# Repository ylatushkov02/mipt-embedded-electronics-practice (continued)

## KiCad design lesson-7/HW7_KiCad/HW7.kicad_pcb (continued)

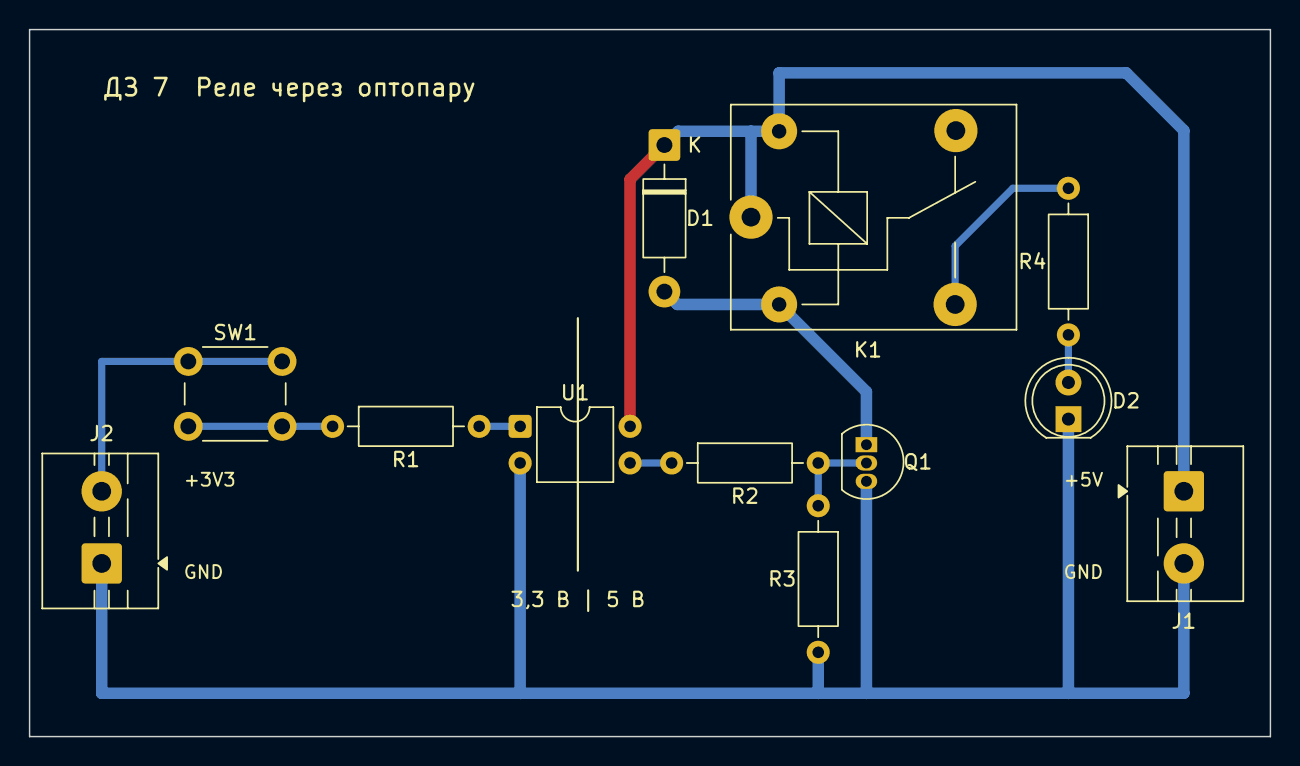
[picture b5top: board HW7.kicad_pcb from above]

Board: 2 copper layers, 86.0 x 49.0 mm, 12 parts (0 on the bottom side), 10 nets.

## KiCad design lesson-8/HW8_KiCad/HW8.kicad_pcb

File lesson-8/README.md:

# ДЗ № 8. Два канала управления реле, питание 12 В через LM317

## Задание
Плата управляет двумя независимыми нагрузками через реле 5 В:
- **Входные сигналы:** 3,3…5 В, ток не более 1…2 мА. Подаются на клеммник `IN1 | GND | IN2`.
- **Питание:** на плату приходит 12 В, напряжение 5 В для реле получается на стабилизаторе LM317T.
- **Выходы:** контакты NC, NO, COM каждого реле выведены на винтовые клеммники.
- **Индикация:** светодиод показывает, что реле включено.
- **Сборка:** монтажная плата, пайка.

## Схема
- **Питание:** U1 LM317T с делителем R1 330 Ом и R2 1 кОм даёт 5,1 В. C1 (0,1 мкФ) и C2 (10 мкФ) — фильтрующие конденсаторы. Жёлтый светодиод D5 с R10 1 кОм показывает, что +5 В есть.
- **Тестовые кнопки:** SW1 и SW2 подают +5 В на IN1 и IN2, чтобы проверить плату без микроконтроллера. Входной ток при нажатии — 1,95 мА. Пока подключён микроконтроллер, кнопки не нажимать.
- **Каналы.** В каждом канале стоит ключ на транзисторе BC547B:
  - сигнал со входа идёт через R3/R6 (2,2 кОм) на базу;
  - R4/R7 (10 кОм) держат транзистор закрытым, если вход ни к чему не подключён;
  - транзистор включает обмотку реле K1/K2 (T73-5VDC) и параллельно ей светодиод D2/D4 с резистором R5/R8 (330 Ом);
  - D1/D3 (1N4007) гасят выброс напряжения на обмотке при выключении.
- **Клеммники:** J1 — вход 12 В, J2 — `IN1 | GND | IN2`, J3/J4 — контакты `NC | NO | COM` реле 1 и 2.

## Расчёт
| Величина | Расчёт | Значение |
|---|---|---|
| Выход LM317 | 1,25 · (1 + 1000/330) + 50 мкА · 1 кОм | **5,09 В** |
| Ток делителя R1 | 1,25 / 330 | 3,8 мА ≥ 3,5 мА (минимальная нагрузка LM317) |
| Ток обмотки (худший случай, 55 Ом) | 5,09 / 55 | 93 мА < 100 мА (максимум BC547) |
| R5, R8 | (5,09 − 2,0 − 0,2) / 10 мА | 289 Ом → **330 Ом** |
| R3, R6 (вход ≤ 2 мА) | (5 − 0,8) / 2 мА | 2,1 кОм → **2,2 кОм** |
| Входной ток | при 5 В / при 3,3 В | 1,9 мА / 1,14 мА |
| Ток базы при 3,3 В | 1,14 − 0,08 (уходит через R4) | 1,06 мА > 93 / 100 = 0,93 мА, транзистор полностью открыт |
| Нагрузка 5 В (оба реле) | 2 · (93 + 8,8) + 3,8 | ≈ 208 мА |
| D5, R10 (индикатор +5 В) | (5,09 − 2,0) / 1 кОм | 3,1 мА; заодно нагружает LM317 до 6,9 мА в покое |
| Мощность LM317 | (12 − 5,09) · 0,208 | ≈ 1,4 Вт, нужен небольшой радиатор |

## Результат
Плата спаяна на монтажной плате 7 × 9 см и работает:
- **Питание:** при подаче 12 В горит жёлтый D5, стабилизатор выдаёт +5 В.
- **Входы:** сигнал 3,3 В подаётся с лабораторного блока питания через кнопки на макетке. Блок показывает ток около 0 А: он меньше 2 мА, поэтому на дисплее не виден.
- **Реле:** кнопка 1 включает реле K1 (щелчок, горит зелёный D2), кнопка 2 включает K2 (щелчок, горит красный D4).
- **Исправление при наладке:** в первой версии рисунка пайки транзисторы BC547 были развёрнуты неправильно (коллектор и эмиттер перепутаны), и реле не включались. Транзисторы развёрнуты плоской стороной вниз, после этого схема заработала.

## Файлы
| Файл | Что это |
|---|---|
| `HW8_KiCad/HW8.kicad_sch` | Принципиальная схема с расчётом, рамка ГОСТ |
| `HW8_KiCad/HW8.kicad_pcb` | Двусторонняя плата 116 × 78,5 мм: дорожки на двух слоях, переходные отверстия, размеры на User.Drawings, пояснения на User.Comments |
| `Схема_ДЗ8_предпросмотр.pdf` | Предпросмотр схемы |
| `Плата_ДЗ8_трассировка_предпросмотр.pdf` | Трассировка и сборочный чертёж |
| `Макетка_два_реле_LM317.png` | Сборка на макетной плате: питание 12 В от лабораторного БП, LM317, два канала реле |
| `Проверка_кнопками_схема_подключения.png` | Дополнительная проверка от 3,3 В: внешние кнопки на макетке подключаются к J2 |
| `Монтажная_плата_схема_пайки.png` | Пайка на монтажной плате 34 × 22 отверстия: вид сверху и вид снизу |
| `Монтажная_плата_итог_внешние_кнопки.png` | Итоговая раскладка пайки собранного варианта |
| `Фото_плата_сверху.png`, `Фото_плата_снизу.png`, `Фото_проверка_3.3В.png` | Фото собранной платы и стенда проверки |
| `Видео_работа_платы.mov` | Видео: кнопки включают реле 1 и 2 |

## Проверка работоспособности
1. Перед подачей питания прозвонить +12V–GND и +5V–GND: короткого замыкания быть не должно.
2. Подать 12 В на J1: загорается жёлтый D5. Мультиметром на C2 должно быть около 5,1 В.
3. Нажать SW1: K1 щёлкает, горит зелёный D2. Отпустить — реле отпускает.
4. Нажать SW2: K2 щёлкает, горит красный D4. Нажать обе — работают оба канала.
5. По желанию подключить нагрузку к COM–NO клеммника J3: она включается кнопкой SW1.
6. Проверка от 3,3 В (как от микроконтроллера) — по схеме `Проверка_кнопками_схема_подключения.png`: внешние кнопки на макетке подключаются к клеммнику J2.

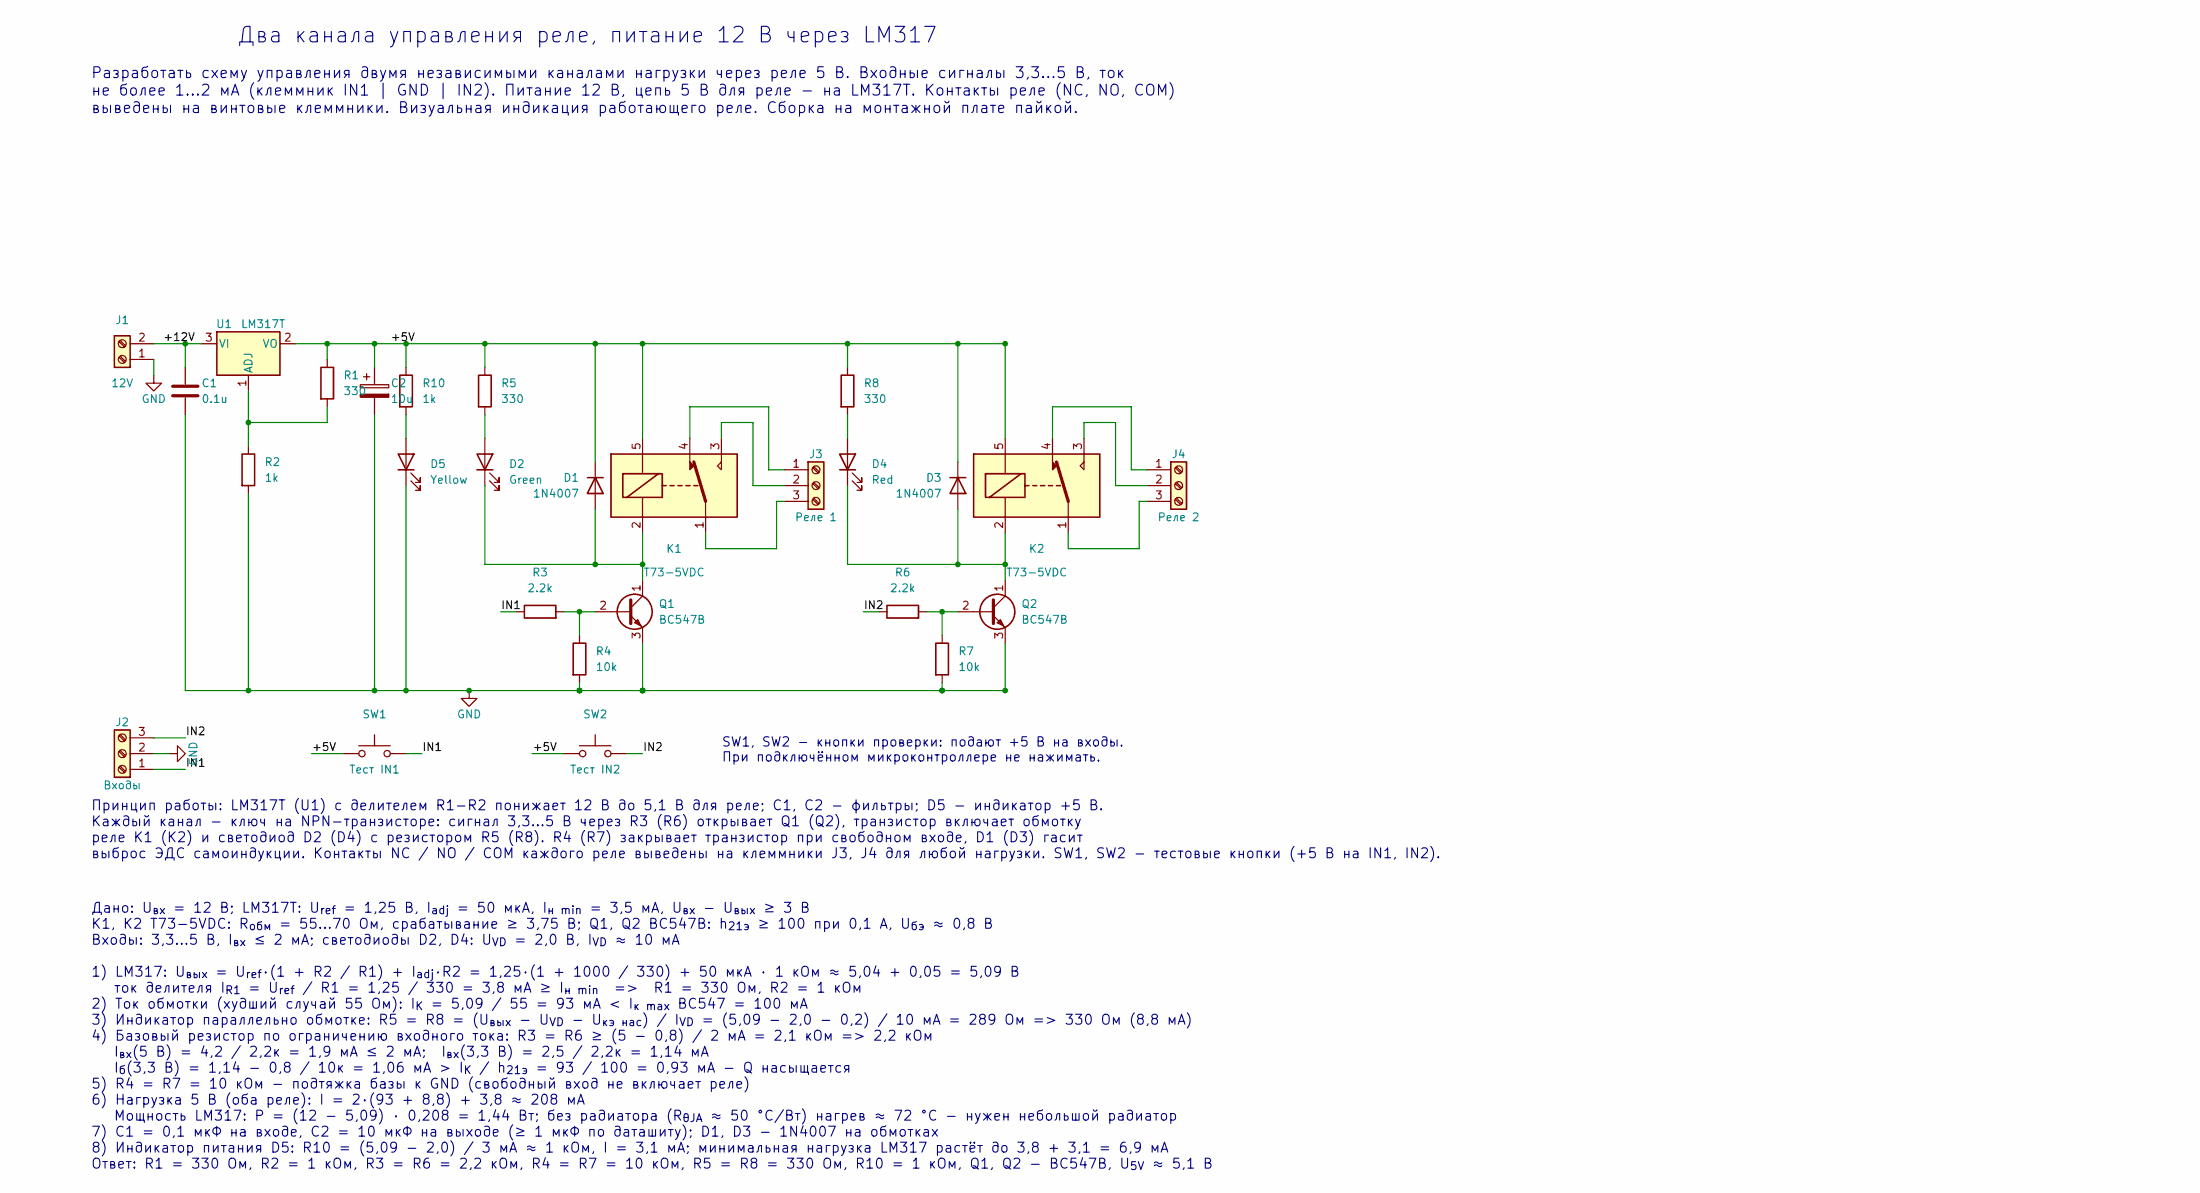
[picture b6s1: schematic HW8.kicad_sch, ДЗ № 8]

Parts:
C1: 0.1u; C_Disc_D5.0mm_W2.5mm_P5.00mm
C2: 10u; CP_Radial_D5.0mm_P2.00mm
D1, D3: 1N4007; D_DO-41_SOD81_P10.16mm_Horizontal
D2: Green; LED_D5.0mm
D4: Red; LED_D5.0mm
D5: Yellow; LED_D5.0mm
J1: 12V; TerminalBlock_MaiXu_MX126-5.0-02P_1x02_P5.00mm
J2: Входы; TerminalBlock_MaiXu_MX126-5.0-03P_1x03_P5.00mm
J3: Реле 1; TerminalBlock_MaiXu_MX126-5.0-03P_1x03_P5.00mm
J4: Реле 2; TerminalBlock_MaiXu_MX126-5.0-03P_1x03_P5.00mm
K1, K2: T73-5VDC; Relay_SPDT_SANYOU_SRD_Series_Form_C
Q1, Q2: BC547B; TO-92L_Inline
R1, R5, R8: 330; R_Axial_DIN0207_L6.3mm_D2.5mm_P10.16mm_Horizontal
R2, R10: 1k; R_Axial_DIN0207_L6.3mm_D2.5mm_P10.16mm_Horizontal
R3, R6: 2.2k; R_Axial_DIN0207_L6.3mm_D2.5mm_P10.16mm_Horizontal
R4, R7: 10k; R_Axial_DIN0207_L6.3mm_D2.5mm_P10.16mm_Horizontal
SW1: Тест IN1; SW_PUSH_6mm
SW2: Тест IN2; SW_PUSH_6mm
U1: LM317T; TO-220-3_Vertical

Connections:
+5V: C2.1, D1.1 (K), D3.1 (K), K1.5, K2.5, R1.1, R5.1, R8.1, R10.1, SW1.1, SW2.1, U1.2 (VO)
+12V: C1.1, J1.2, U1.3 (VI)
ADJ: R1.2, R2.1, U1.1 (ADJ)
B1: Q1.2 (B), R3.2, R4.1
B2: Q2.2 (B), R6.2, R7.1
COL1: D1.2 (A), D2.1 (K), K1.2, Q1.1 (C)
COL2: D3.2 (A), D4.1 (K), K2.2, Q2.1 (C)
COM1: J3.3, K1.1
COM2: J4.3, K2.1
GND: C1.2, C2.2, D5.1 (K), J1.1, J2.2, Q1.3 (E), Q2.3 (E), R2.2, R4.2, R7.2
IN1: J2.1, R3.1, SW1.2
IN2: J2.3, R6.1, SW2.2
LEDA1: D2.2 (A), R5.2
LEDA2: D4.2 (A), R8.2
NC1: J3.1, K1.4
NC2: J4.1, K2.4
NO1: J3.2, K1.3
NO2: J4.2, K2.3
PWRLED: D5.2 (A), R10.2

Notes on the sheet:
Два канала управления реле, питание 12 В через LM317
Разработать схему управления двумя независимыми каналами нагрузки через реле 5 В. Входные сигналы 3,3...5 В, ток не более 1...2 мА (клеммник IN1 | GND | IN2). Питание 12 В, цепь 5 В для реле - на LM317T. Контакты реле (NC, NO, COM) выведены на винтовые клеммники. Визуальная индикация работающего ре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
SW1, SW2 - кнопки проверки: подают +5 В на входы. При подключённом микроконтроллере не нажимать.
Принцип работы: LM317T (U1) с делителем R1-R2 понижает 12 В до 5,1 В для реле; C1, C2 - фильтры; D5 - индикатор +5 В. Каждый канал - ключ на NPN-транзисторе: сигнал 3,3...5 В через R3 (R6) открывает Q1 (Q2), транзистор включает обмотку реле K1 (K2) и светодиод D2 (D4) с резистором R5 (R8). R4 (R7) 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
Дано: U_{вх} = 12 В; LM317T: U_{ref} = 1,25 В, I_{adj} = 50 мкА, I_{н min} = 3,5 мА, U_{вх} - U_{вых} ≥ 3 В K1, K2 T73-5VDC: R_{обм} = 55...70 Ом, срабатывание ≥ 3,75 В; Q1, Q2 BC547B: h_{21э} ≥ 100 при 0,1 А, U_{бэ} ≈ 0,8 В Входы: 3,3...5 В, I_{вх} ≤ 2 мА; светодиоды D2, D4: U_{VD} = 2,0 В, I_{VD}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

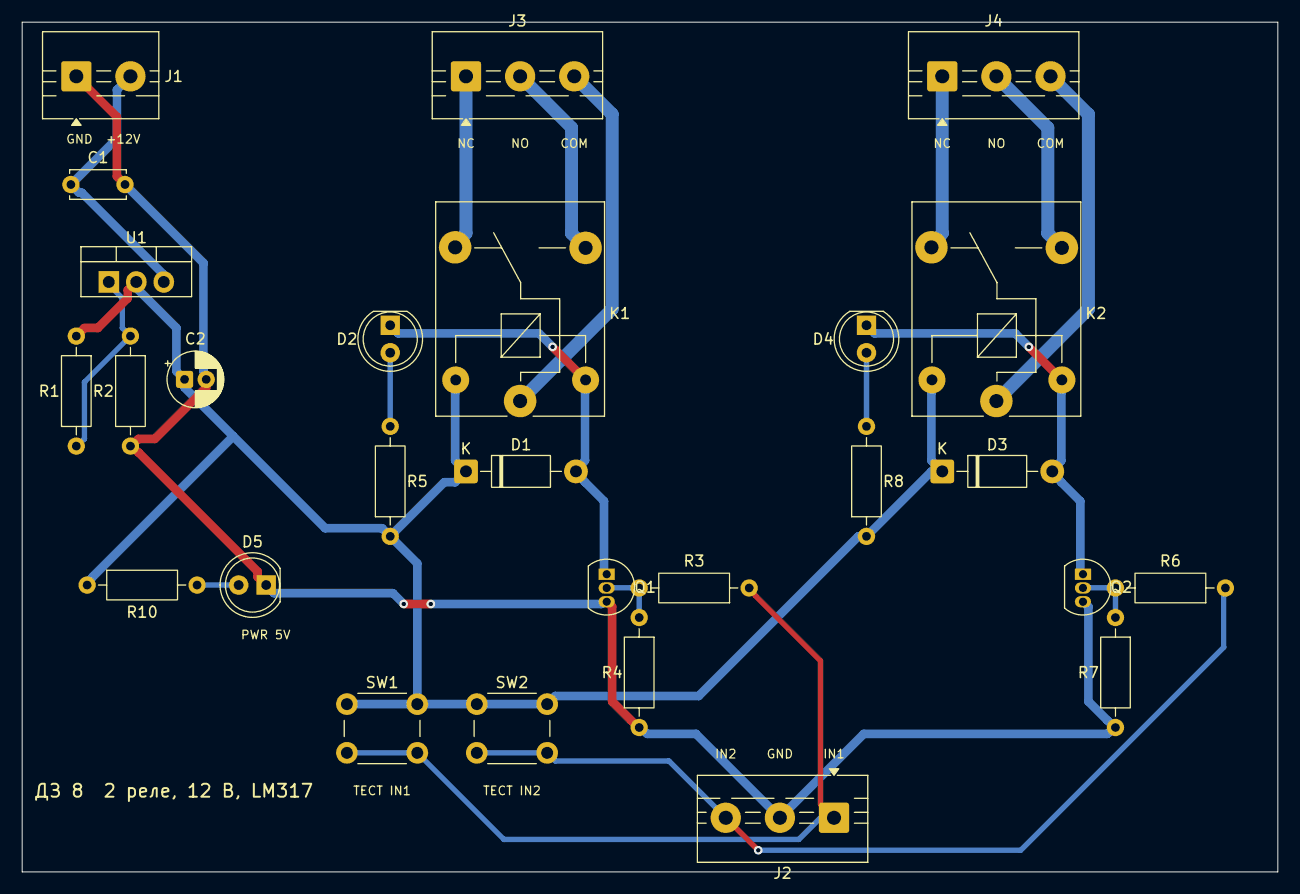
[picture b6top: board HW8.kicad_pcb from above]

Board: 2 copper layers, 116.0 x 78.5 mm, 27 parts (0 on the bottom side), 19 nets.

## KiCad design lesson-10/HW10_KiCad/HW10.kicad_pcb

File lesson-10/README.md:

# ДЗ №10. ШИМ-регулятор нагрузки 12 В

Открывать `HW10_KiCad/HW10.kicad_pro`. В проект входят актуальная схема `HW10.kicad_sch`, плата `HW10.kicad_pcb`. Схема содержит встроенные символы. Корпусам назначены стандартные 3D-модели установленного KiCad 10.

## Работа схемы

J1 принимает 12 В. LM317T U1 формирует около 5 В для таймера и драйвера. R1 = 120 Ом между OUT и ADJ, R2 = 360 Ом между ADJ и GND. Расчёт `1,25 × (1 + 360/120) = 5 В`. Ток делителя 10,4 мА обеспечивает минимальную нагрузку стабилизатора. C1 и C3 по 100 нФ подавляют высокочастотные помехи. C2 — выходной электролит 10 мкФ / 16 В.

U2 NE555P или NA555P формирует ШИМ. Выводы 2 и 6 соединены с C5 100 нФ. R3 1 кОм подключён от +5V к выводу 7 и движку RV1. При заряде ток идёт через одну часть RV1 и D1. При разряде — через другую часть RV1 и D2. RV1 50 кОм изменяет заполнение. RV2 50 кОм включён реостатом, движок соединён с выводом 3. R4 1 кОм ограничивает ток при крайнем положении RV2. RESET соединён с +5V, CONT зашунтирован C4 10 нФ.

Для идеальных диодов оценка частоты `f ≈ 1 / [0,693 × C5 × (R3 + RV1 + 2 × (RV2 + R4))]` даёт около 94–272 Гц при C5 = 100 нФ. Реальные диоды и выход DISCH изменяют результат. Частоту и заполнение измеряют после сборки. Для медленной демонстрации C5 можно заменить на 1–4,7 мкФ с соблюдением полярности электролита.

Вывод 3 таймера через R5 1 кОм напрямую раскачивает объединённые базы Q1 BC547B и Q2 BC557B, образующих двухтактный эмиттерный повторитель — требуемый заданием драйвер MOSFET. Эмиттеры объединены в цепь DRIVE. Коллектор Q1 идёт к +5V, коллектор Q2 к GND. R7 47 Ом соединяет DRIVE и затвор Q3. R8 10 кОм удерживает затвор у GND при отключённом драйвере.

Выбран логический MOSFET IRLZ44N. Верхний уровень на затворе — выход NE555 при питании 5 В (около 3,3–4 В) минус переход база-эмиттер повторителя, то есть порядка 2,7–3,3 В. При таком напряжении сопротивление открытого канала IRLZ44N следует проверять под выбранной нагрузкой. Для макетной демонстрации подходит маломощная светодиодная нагрузка с ограничением тока. Q3 коммутирует нагрузку по низкой стороне. Нагрузка подключается между J2.1 (+12V) и J2.2 (LOAD_NEG). D3 1N4007 включён катодом к +12V и анодом к LOAD_NEG для защиты при индуктивной нагрузке. Ток нагрузки выбирают с учётом диода, проводников и нагрева. Данные производителя приведены на https://www.infineon.com/part/IRLZ44N .

## Сборка макета

Точные отверстия для деталей, питания, нагрузки и всех перемычек перечислены в [монтажной карте](Макетка_ДЗ10.md).

1. Открыть `Макетка_ДЗ10_сборка.png`. Вся сборка занимает столбцы 1–31 макетки на 830 контактов. Слева стоит стабилизатор U1, у центрального паза — таймер U2 с меткой вывода 1 у f14, справа — драйвер и ключ Q3.
2. По `Макетка_ДЗ10_выводы.png` установить каждый вывод в указанное отверстие. RV1 и RV2 рассчитаны на три жёсткие ножки в ряд с шагом 2,54 мм. Выводы 1, 2 и 3 RV1 вставить в j5, j6 и j7, а RV2 — в j11, j12 и j13. Средняя ножка каждого регулятора — движок. J1/J2 обозначают внешние подключения проводами.
3. Установить 22 перемычки по карте `Макетка_ДЗ10_перемычки.png`. В каждом столбце отверстия a–e соединены внутри платы. Отверстия f–j образуют отдельную группу. Короткая перемычка f12 ↔ f13 соединяет выводы 2 и 3 RV2 для работы в режиме реостата.
4. Использовать левые секции шин. Верхняя плюсовая шина P12 питает нагрузку от 12 В, нижняя P5 получает 5 В с выхода LM317. Верхняя и нижняя шины GND соединяются перемычкой e19 ↔ f22; верхняя GND задействована на столбцах 7, 12, 19 и 30, нижняя — на 15 и 22. Число в квадратных скобках у шины указывает столбец центрального поля напротив гнезда. Если отверстия шин смещены, выбрать свободное гнездо той же непрерывной секции.
5. Сначала собрать U1, R1/R2, C1–C3 и все перемычки питания и GND. Подать 12 В на J1. Относительно верхней GND проверить около 12 В в свободном гнезде d6 и около 5 В в e5 и на шине P5.
6. После отключения питания установить таймер, времязадающую цепь и драйвер. Проверить импульсы на выводе 3 U2 и на затворе Q3.
7. При снятом питании подключить пробную нагрузку между верхней шиной +12 В [30] и a29. Полоса диода D3 должна быть со стороны b26 (+12 В), противоположный вывод — в b29 (сток Q3). Подать питание и проверить регулировку RV1/RV2 до пайки.

Цепи карты макетки сформированы из того же списка соединений, что схема и плата. Для каждого столбца автоматически проверено отсутствие смешения разных цепей.

## Файлы и проверка

`Схема_ДЗ10.pdf` получен прямым экспортом электрической схемы KiCad. `Плата_3D_вид.png` получен штатным 3D-рендерером KiCad с моделями всех 24 корпусов.

PCB разведена, контур 147 × 50 мм. Проверка DRC с сопоставлением со схемой дала 0 нарушений, 0 неподключённых площадок и 0 расхождений со схемой. Физические сборка, измерения и пайка остаются практической частью задания.

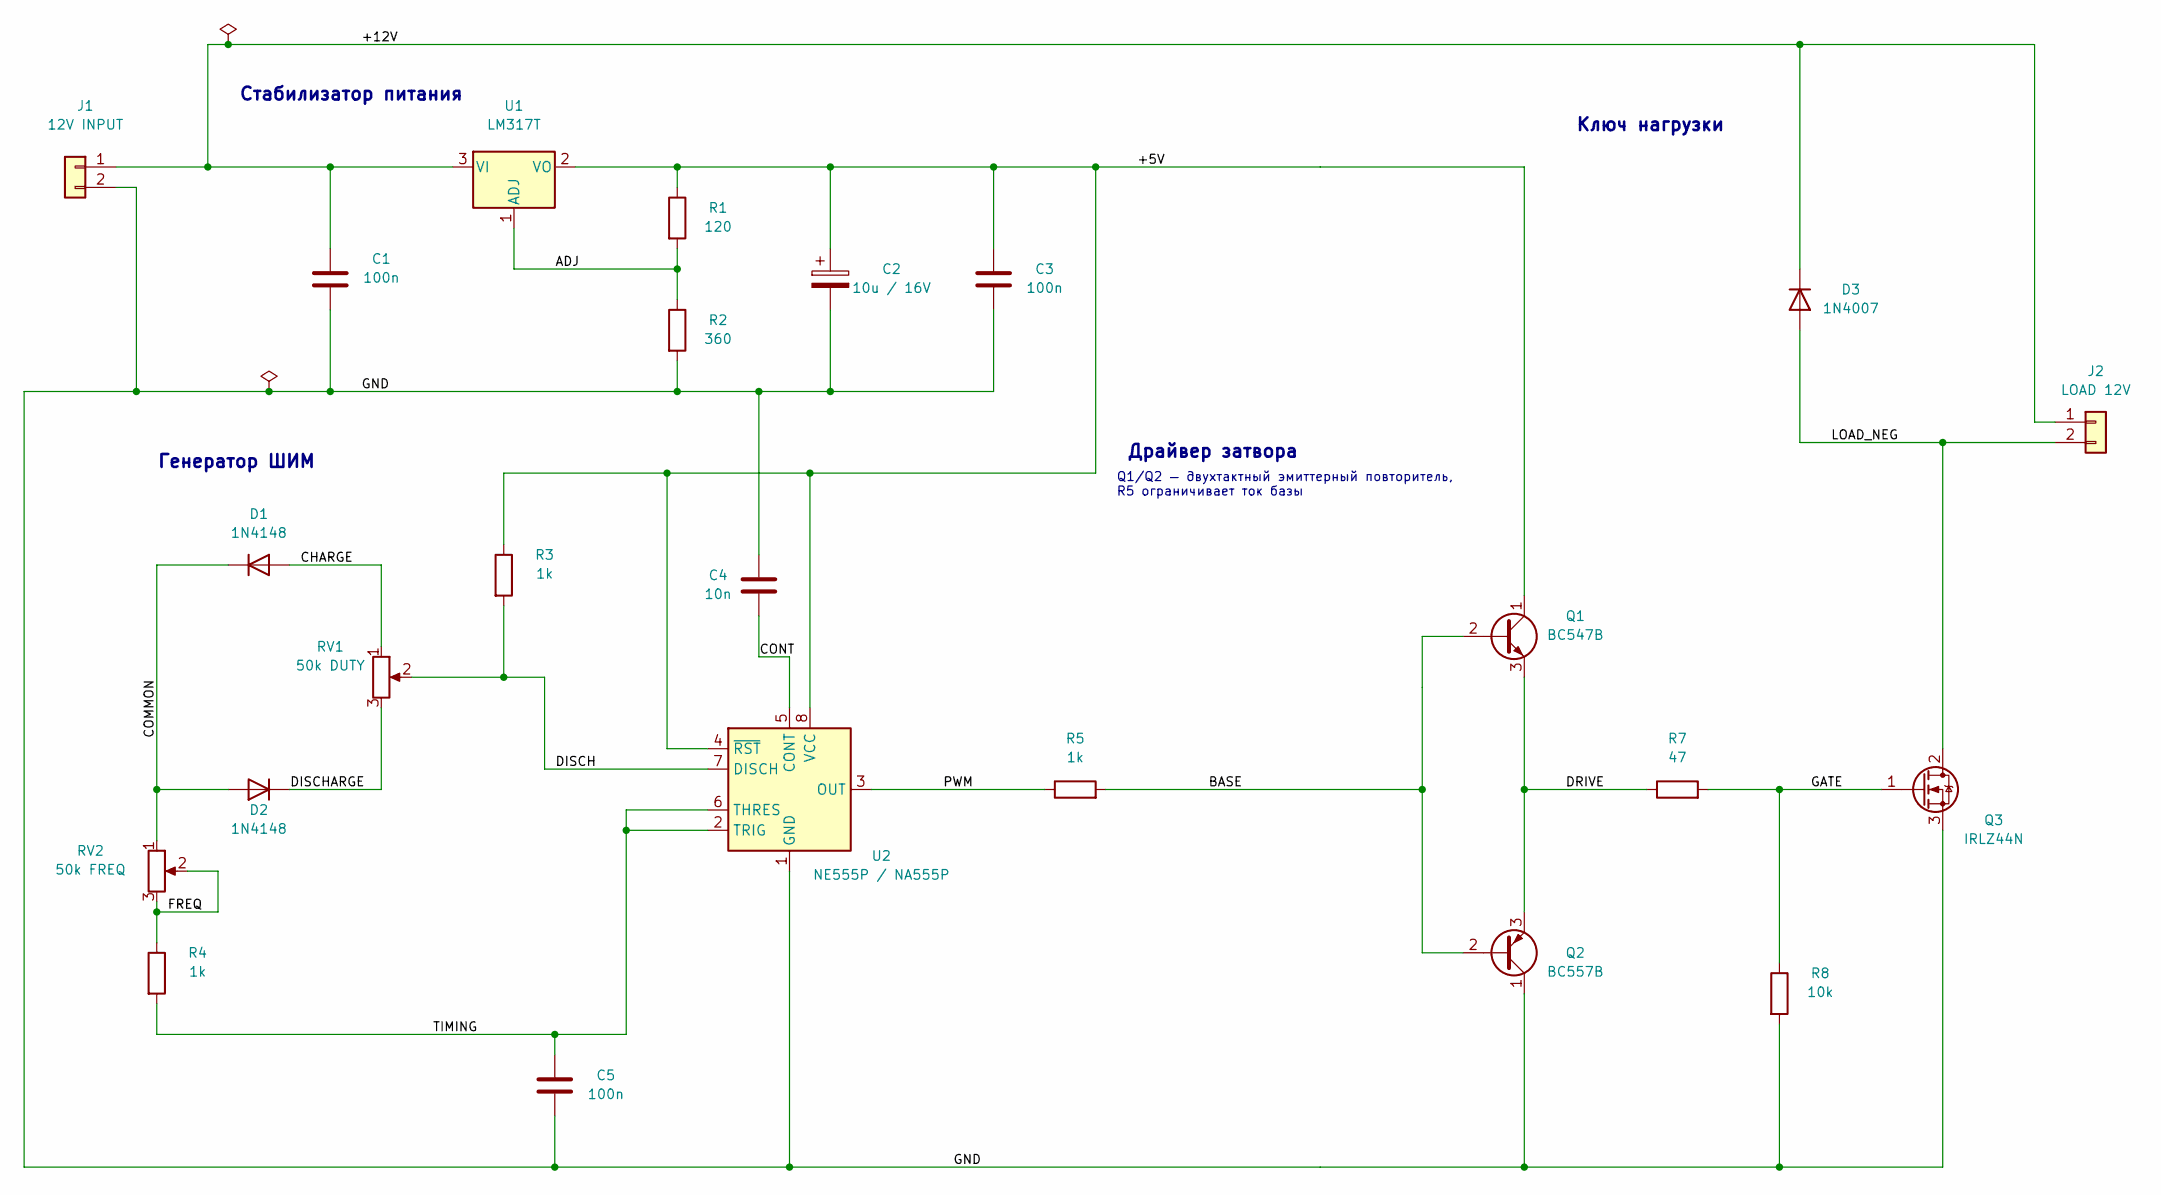
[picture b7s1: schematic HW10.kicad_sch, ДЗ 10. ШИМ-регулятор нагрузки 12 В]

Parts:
C1, C3, C5: 100n; C_Disc_D5.0mm_W2.5mm_P5.00mm
C2: 10u / 16V; CP_Radial_D5.0mm_P2.00mm
C4: 10n; C_Disc_D5.0mm_W2.5mm_P5.00mm
D1, D2: 1N4148; D_DO-35_SOD27_P7.62mm_Horizontal
D3: 1N4007; D_DO-41_SOD81_P10.16mm_Horizontal
J1: 12V INPUT; TerminalBlock_Phoenix_MKDS-1,5-2-5.08_1x02_P5.08mm_Horizont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
J2: LOAD 12V; TerminalBlock_Phoenix_MKDS-1,5-2-5.08_1x02_P5.08mm_Horizont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
Q1: BC547B; TO-92_Inline
Q2: BC557B; TO-92_Inline
Q3: IRLZ44N; TO-220-3_Vertical
R1: 120; R_Axial_DIN0207_L6.3mm_D2.5mm_P7.62mm_Horizontal
R2: 360; R_Axial_DIN0207_L6.3mm_D2.5mm_P7.62mm_Horizontal
R3, R4, R5: 1k; R_Axial_DIN0207_L6.3mm_D2.5mm_P7.62mm_Horizontal
R7: 47; R_Axial_DIN0207_L6.3mm_D2.5mm_P7.62mm_Horizontal
R8: 10k; R_Axial_DIN0207_L6.3mm_D2.5mm_P7.62mm_Horizontal
RV1: 50k DUTY; Potentiometer_Bourns_3296W_Vertical
RV2: 50k FREQ; Potentiometer_Bourns_3296W_Vertical
U1: LM317T; TO-220-3_Vertical
U2: NE555P / NA555P; DIP-8_W7.62mm

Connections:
/+5V: C2.1, C3.1, Q1.1 (C), R1.1, R3.1, U1.2 (VO), U2.4 (~RST), U2.8 (VCC)
/+12V: C1.1, D3.1 (K), J1.1, J2.1, U1.3 (VI)
/ADJ: R1.2, R2.1, U1.1 (ADJ)
/BASE: Q1.2 (B), Q2.2 (B), R5.2
/CHARGE: D1.2 (A), RV1.1
/COMMON: D1.1 (K), D2.2 (A), RV2.1
/CONT: C4.1, U2.5 (CONT)
/DISCH: R3.2, RV1.2, U2.7 (DISCH)
/DISCHARGE: D2.1 (K), RV1.3
/DRIVE: Q1.3 (E), Q2.3 (E), R7.1
/FREQ: R4.1, RV2.2, RV2.3
/GATE: Q3.1 (G), R7.2, R8.1
/GND: C1.2, C2.2, C3.2, C4.2, C5.2, J1.2, Q2.1 (C), Q3.3 (S), R2.2, R8.2, U2.1 (GND)
/LOAD_NEG: D3.2 (A), J2.2, Q3.2 (D)
/PWM: R5.1, U2.3 (OUT)
/TIMING: C5.1, R4.2, U2.2 (TRIG), U2.6 (THRES)

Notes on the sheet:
Стабилизатор питания
Генератор ШИМ
Драйвер затвора
Ключ нагрузки
Q1/Q2 — двухтактный эмиттерный повторитель, R5 ограничивает ток базы

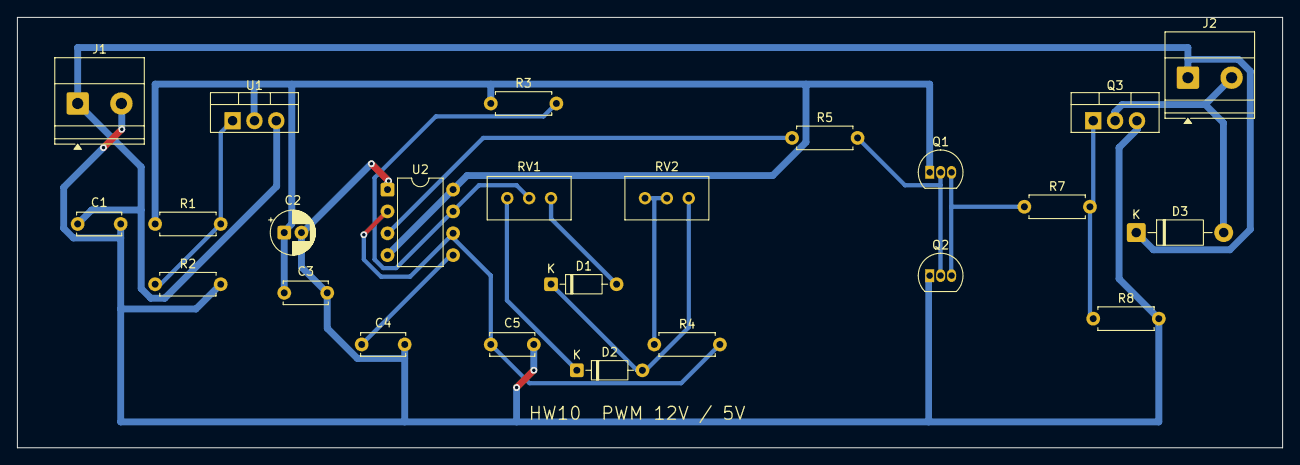
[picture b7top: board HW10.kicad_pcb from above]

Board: 2 copper layers, 147.0 x 50.0 mm, 24 parts (0 on the bottom side), 16 nets.
